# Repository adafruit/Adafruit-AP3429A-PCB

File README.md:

## Adafruit AP3429A Buck Converter Breakout PCB

<a href="http://www.adafruit.com/products/4711"><br/>
Click here to purchase one from the Adafruit shop</a>

PCB files for the Adafruit AP3429A Buck Converter Breakout. 

Format is EagleCAD schematic and board layout
* https://www.adafruit.com/product/4711

### Description

This little buck converter based on the AP3429A is super handy, taking up to 5.5V input and providing a 3.3V output with up to 1.2A current. It's great for supplying power to popular 3.3V voltage circuits from a range of battery or power options.  This chip provides up to 1.2 Amp load current across the entire input voltage range of 3.4 to 5.5V. It's not a huge range but does cover LiPoly batteries, 3 alkalines, and USB power.

Great for your portable project, we made this "pin compatible" with the LM1117-3.3V TO-220 chip so you can swap it in for better performance (90-95% efficiency!) There's also an ENable pin, tie it low to shut down the output completely.

The Adafruit AP3429A Breakout runs at 1-MHz fixed-frequency. Even though the chip itself supports up to 2A, the inductor we used is small and so the breakout can only provide about 1.2 Amps.

### License

Adafruit invests time and resources providing this open source design, please support Adafruit and open-source hardware by purchasing products from [Adafruit](https://www.adafruit.com)!

Designed by Limor Fried/Ladyada for Adafruit Industries.

Creative Commons Attribution/Share-Alike, all text above must be included in any redistribution. 
See license.txt for additional details.

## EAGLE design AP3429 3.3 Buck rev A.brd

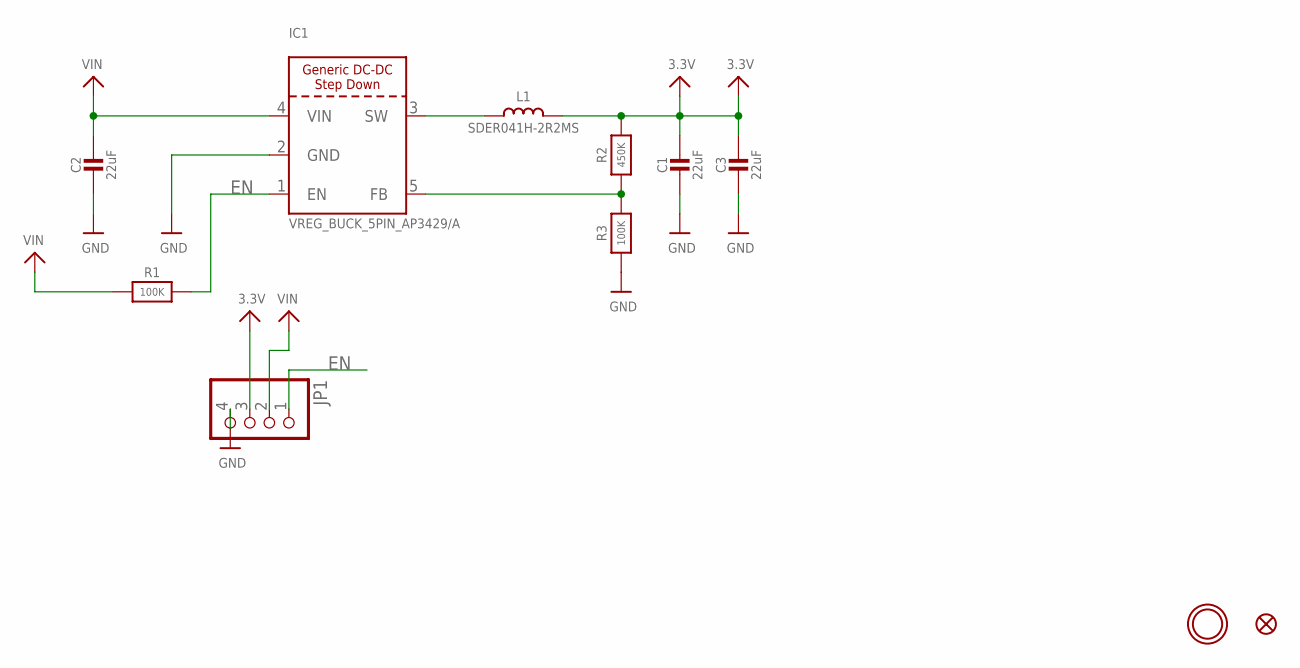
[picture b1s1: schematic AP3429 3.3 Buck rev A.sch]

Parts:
C1, C2, C3: 22uF; 0805-NO
FID1: FIDUCIAL_1MM
IC1: VREG_BUCK_5PIN_AP3429/A; SOT23-5
JP1: HEADER-1X4ROUND; 1X04_ROUND
L1: SDER041H-2R2MS; INDUCTOR_TAIYOYUDEN_NRH2412T
R1, R3: 100K; 0603-NO
R2: 450K; 0603-NO
U$9: MOUNTINGHOLE2.5; MOUNTINGHOLE_2.5_PLATED

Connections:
3.3V: C1.1, C3.1, JP1.3, L1.2, R2.2
EN: IC1.1 (EN), JP1.1, R1.2
FB: IC1.5 (FB), R2.1, R3.2
GND: C1.2, C2.2, C3.2, IC1.2 (GND), JP1.4, R3.1
unnamed: IC1.3 (SW), L1.1
VIN: C2.1, IC1.4 (VIN), JP1.2, R1.1

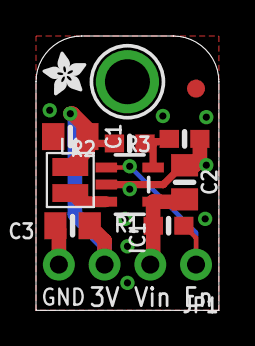
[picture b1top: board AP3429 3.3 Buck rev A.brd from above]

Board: 2 copper layers, 10.2 x 15.2 mm, 13 parts (1 on the bottom side), 6 nets.

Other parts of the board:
U$10: PCBFEAT-REV-040
U$11: ADAFRUIT_2.5MM

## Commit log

2020-09-02 Added board files
2020-09-02 Added rev file

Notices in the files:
parts and their libraries:
microbuilder: This work is placed in the public domain, and may be freely used for commercial and non-commercial work with the following conditions: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
